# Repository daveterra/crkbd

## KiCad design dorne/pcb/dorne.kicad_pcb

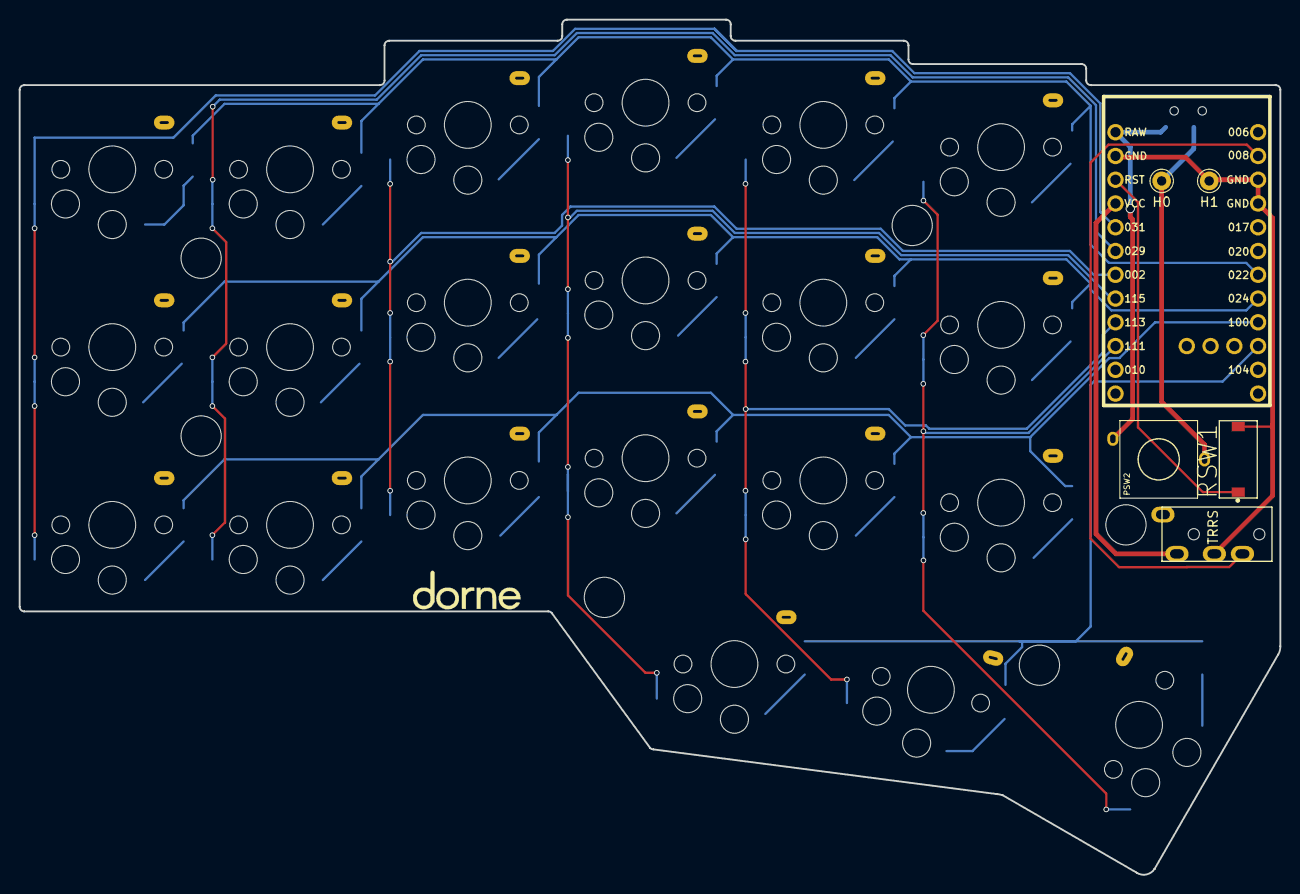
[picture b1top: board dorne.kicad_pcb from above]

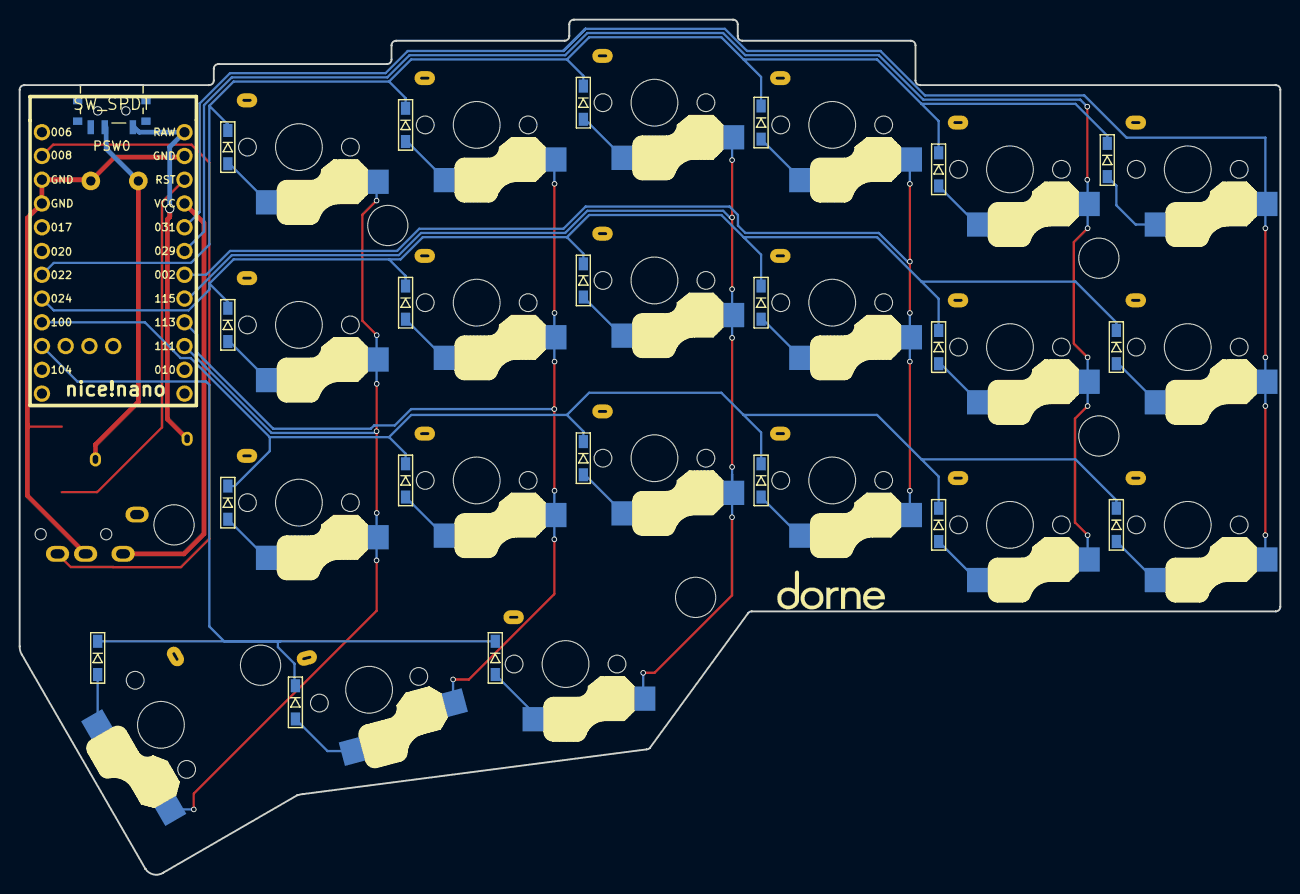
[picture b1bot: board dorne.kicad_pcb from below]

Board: 2 copper layers, 134.8 x 91.4 mm, 57 parts (24 on the bottom side), 37 nets.

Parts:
D1, D2, D3, D4, D5, D6, D7, D8, D9, D10, D11, D12, D13, D14, D15, D16, D17, D18, D19, D20, D21: D; D3_SMD_v2
H0, H1: MountingHole_Pad; Pin_D1.0mm_L10.0mm
J1: MJ-4PP-9; MJ-4PP-9_1side
LOGO1, LOGO2: LOGO; dorne-logo-horizontal
MH1, MH2, MH3, MH4, MH5, MH6: Val**; M2_HOLE_v2
PSW0: SW_SPDT; ALPS-SSSS811101-0
PSW2: SW_SPST; SW_L068-A
RSW1: SW_PUSH; CK_Components-KSR223GNCLFG-0
SW1, SW2, SW3, SW4, SW5, SW6, SW7, SW8, SW9, SW10, SW11, SW12, SW13, SW14, SW15, SW16, SW17, SW18, SW19, SW20: SW_PUSH; ChocV1_V2_Hotswap
SW21: SW_PUSH; ChocV1_V2_Hotswap_1.5u
U3: nice_nano

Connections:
GND: H1.1, J1.C, RSW1.2, U3.3 (GND), U3.4 (GND), U3.23 (GND)
unnamed: D1.2 (A), SW1.2
unnamed: D2.2 (A), SW2.2
unnamed: D3.2 (A), SW3.2
unnamed: D4.2 (A), SW4.2
unnamed: D5.2 (A), SW5.2
unnamed: D6.2 (A), SW6.2
unnamed: D7.2 (A), SW7.2
unnamed: D8.2 (A), SW8.2
unnamed: D9.2 (A), SW9.2
unnamed: D10.2 (A), SW10.2
unnamed: D11.2 (A), SW11.2
unnamed: D12.2 (A), SW12.2
unnamed: D13.2 (A), SW13.2
unnamed: D14.2 (A), SW14.2
unnamed: D15.2 (A), SW15.2
unnamed: D16.2 (A), SW16.2
unnamed: D17.2 (A), SW17.2
unnamed: D18.2 (A), SW18.2
unnamed: D19.2 (A), SW19.2
unnamed: D20.2 (A), SW20.2
unnamed: D21.2 (A), SW21.2
VCC: J1.D, U3.21 (VCC)
bat_in: PSW0.1 (A), PSW2.2 (B), U3.24 (BATIN/P0.04)
bat_pos: H0.1, PSW0.2 (B), PSW2.1 (A)
col0: SW1.1, SW7.1, SW13.1, U3.20 (AIN7/P0.31)
col1: SW2.1, SW8.1, SW14.1, U3.19 (AIN5/P0.29)
col2: SW3.1, SW9.1, SW15.1, U3.18 (AIN0/P0.02)
col3: SW4.1, SW10.1, SW16.1, SW19.1, U3.17 (P1.15)
col4: SW5.1, SW11.1, SW17.1, SW20.1, U3.16 (P1.13)
col5: SW6.1, SW12.1, SW18.1, SW21.1, U3.15 (P1.11)
data: J1.B, U3.2 (RX1/P0.08)
reset: RSW1.1, U3.22 (RST)
row0: D1.1 (K), D2.1 (K), D3.1 (K), D4.1 (K), D5.1 (K), D6.1 (K), U3.7 (P0.22)
row1: D7.1 (K), D8.1 (K), D9.1 (K), D10.1 (K), D11.1 (K), D12.1 (K), U3.8 (P0.24)
row2: D13.1 (K), D14.1 (K), D15.1 (K), D16.1 (K), D17.1 (K), D18.1 (K), U3.9 (P1.00)
row3: D19.1 (K), D20.1 (K), D21.1 (K), U3.10 (P0.11)

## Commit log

2023-07-09 Make a copy of corne-cherry
2023-07-09 Rename project files
2023-07-09 Add Nice-Nano
2023-07-09 RM LEDs
2023-07-10 cherry->choc
2023-07-10 Update name in PCB
2023-07-10 Starting to integrate nice nano
2023-07-10 Fix Diode issue
2023-07-12 Left half is routed better now
2023-07-12 Better routing
2023-07-14 Reset and power WIP
2023-07-14 Saving state
2023-07-15 Finished everything??
2023-07-17 Trying to fix the edge cuts and add back in the M2 holes
2023-07-17 Realigned everything!!!!
2023-07-17 I think it's done?
2023-07-18 JLC Submitted versino
2023-07-18 Adding top and bottom
2023-09-12 Saving so I can look at my old files
